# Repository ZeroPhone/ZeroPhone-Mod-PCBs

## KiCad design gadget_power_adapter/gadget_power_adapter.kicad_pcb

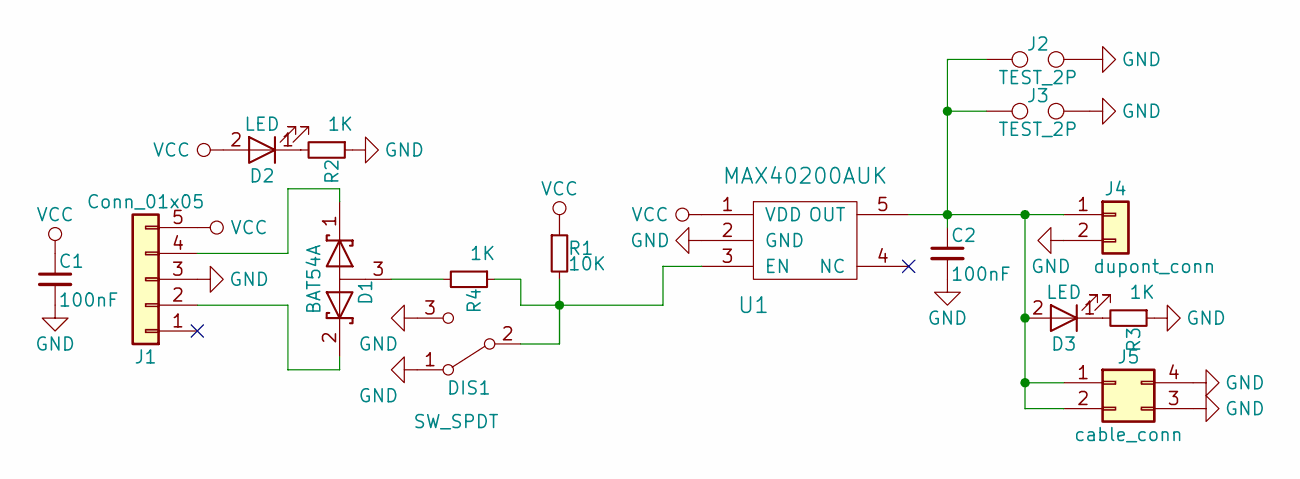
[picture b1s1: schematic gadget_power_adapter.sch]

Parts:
C1, C2: 100nF; C_0603
D1: BAT54A; SOT-23
D2, D3: LED; LED_0805
DIS1: SW_SPDT; SW_SPDT_PCM12
J1: Conn_01x05; Pin_Header_Angled_1x05_Pitch2.54mm
J2, J3: TEST_2P; Test_Point_2Pads
J4: dupont_conn; Pin_Header_Angled_1x02_Pitch2.54mm
J5: cable_conn; Pin_Header_Straight_2x02_Pitch2.54mm
R1: 10K; R_0603
R2, R3, R4: 1K; R_0603
U1: MAX40200AUK; SOT-23-5

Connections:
GND: C1.2, C2.2, DIS1.1 (A), DIS1.3 (C), J1.3, J2.2, J3.2, J4.2, J5.3, J5.4, R2.1, R3.1, U1.2 (GND)
unnamed: C2.1, D3.2 (A), J2.1, J3.1, J4.1, J5.1, J5.2, U1.5 (OUT)
unnamed: D1.1 (K), J1.4
unnamed: D1.2 (K), J1.2
unnamed: D1.3 (A), R4.2
unnamed: D2.1 (K), R2.2
unnamed: D3.1 (K), R3.2
unnamed: DIS1.2 (B), R1.2, R4.1, U1.3 (EN)
VCC: C1.1, D2.2 (A), J1.5, R1.1, U1.1 (VDD)

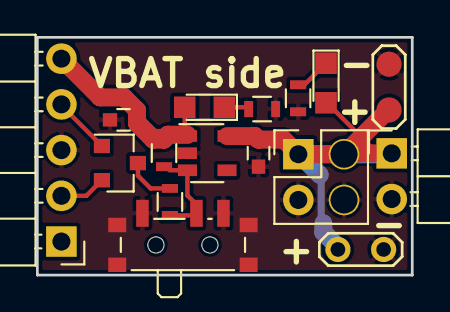
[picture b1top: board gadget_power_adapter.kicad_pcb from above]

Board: 2 copper layers, 20.8 x 13.2 mm, 16 parts (0 on the bottom side), 9 nets.

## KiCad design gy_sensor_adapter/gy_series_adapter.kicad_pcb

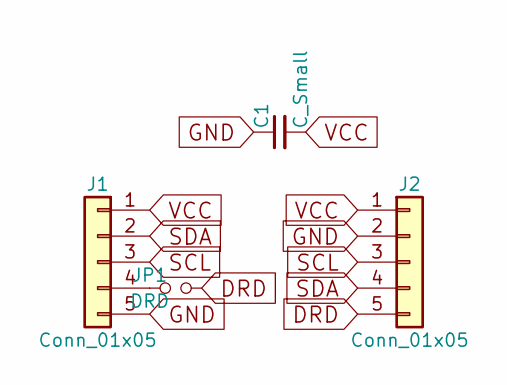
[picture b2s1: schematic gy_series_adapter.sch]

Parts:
C1: C_Small; C_0603
J1, J2: Conn_01x05; Pin_Header_Straight_1x05_Pitch2.54mm
JP1: DRD; GS2_SMALL

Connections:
DRD: J2.5, JP1.2
GND: C1.1, J1.5, J2.2
unnamed: J1.4, JP1.1
SCL: J1.3, J2.3
SDA: J1.2, J2.4
VCC: C1.2, J1.1, J2.1

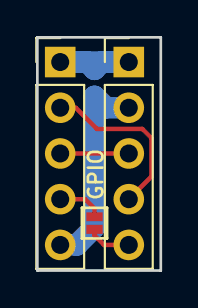
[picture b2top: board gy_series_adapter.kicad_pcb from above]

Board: 2 copper layers, 6.9 x 13.0 mm, 4 parts (1 on the bottom side), 6 nets.

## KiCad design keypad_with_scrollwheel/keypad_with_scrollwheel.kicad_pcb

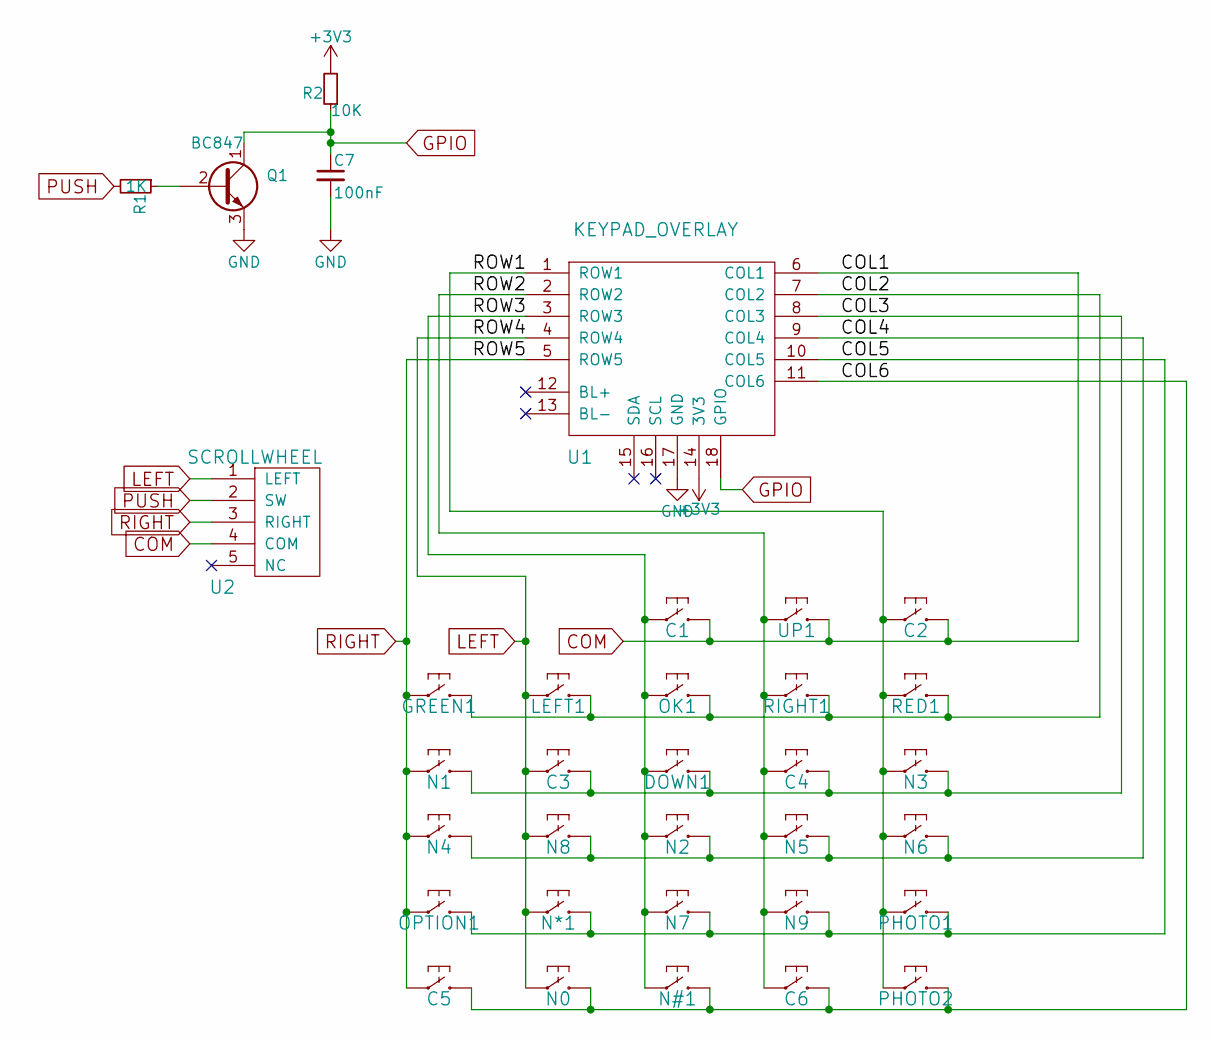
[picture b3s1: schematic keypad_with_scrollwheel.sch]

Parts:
C1, C2, C3, C4, C5, C6: AB2_SWITCH_MOMENTARY; SW_SPST_EVQPE1
C7: 100nF; C_0805
DOWN1: AB2_SWITCH_MOMENTARY; SW_SPST_SKQG
GREEN1: AB2_SWITCH_MOMENTARY; SW_SPST_EVQPE1
LEFT1: AB2_SWITCH_MOMENTARY; SW_SPST_SKQG
N0, N1, N2, N3, N4, N5, N6, N7, N8, N9: AB2_SWITCH_MOMENTARY; SW_SPST_SKQG
N#1: AB2_SWITCH_MOMENTARY; SW_SPST_SKQG
N*1: AB2_SWITCH_MOMENTARY; SW_SPST_SKQG
OK1: AB2_SWITCH_MOMENTARY; SW_SPST_SKQG
OPTION1: AB2_SWITCH_MOMENTARY; SW_SPST_EVQP7C
PHOTO1, PHOTO2: AB2_SWITCH_MOMENTARY; SW_SPST_EVQP7C
Q1: BC847; SOT-23_Handsoldering
R1: 1K; R_0805_HandSoldering
R2: 10K; R_0805_HandSoldering
RED1: AB2_SWITCH_MOMENTARY; SW_SPST_EVQPE1
RIGHT1: AB2_SWITCH_MOMENTARY; SW_SPST_SKQG
U1: KEYPAD_OVERLAY; keypad_overlay
U2: SCROLLWHEEL
UP1: AB2_SWITCH_MOMENTARY; SW_SPST_SKQG

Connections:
+3V3: R2.2, U1.14 (3V3)
/COL2: GREEN1.2, LEFT1.2, OK1.2, RED1.2, RIGHT1.2, U1.7 (COL2)
/COL3: C3.2, C4.2, DOWN1.2, N1.2, N3.2, U1.8 (COL3)
/COL4: N2.2, N4.2, N5.2, N6.2, N8.2, U1.9 (COL4)
/COL5: N7.2, N9.2, N*1.2, OPTION1.2, PHOTO1.2, U1.10 (COL5)
/COL6: C5.2, C6.2, N0.2, N#1.2, PHOTO2.2, U1.11 (COL6)
/ROW1: C2.1, N3.1, N6.1, PHOTO1.1, PHOTO2.1, RED1.1, U1.1 (ROW1)
/ROW2: C4.1, C6.1, N5.1, N9.1, RIGHT1.1, U1.2 (ROW2), UP1.1
/ROW3: C1.1, DOWN1.1, N2.1, N7.1, N#1.1, OK1.1, U1.3 (ROW3)
COM: C1.2, C2.2, U1.6 (COL1), U2.4 (COM), UP1.2
GND: C7.2, Q1.3 (E), U1.17 (GND)
GPIO: C7.1, Q1.1 (C), R2.1, U1.18 (GPIO)
LEFT: C3.1, LEFT1.1, N0.1, N8.1, N*1.1, U1.4 (ROW4), U2.1 (LEFT)
unnamed: Q1.2 (B), R1.1
PUSH: R1.2, U2.2 (SW)
RIGHT: C5.1, GREEN1.1, N1.1, N4.1, OPTION1.1, U1.5 (ROW5), U2.3 (RIGHT)

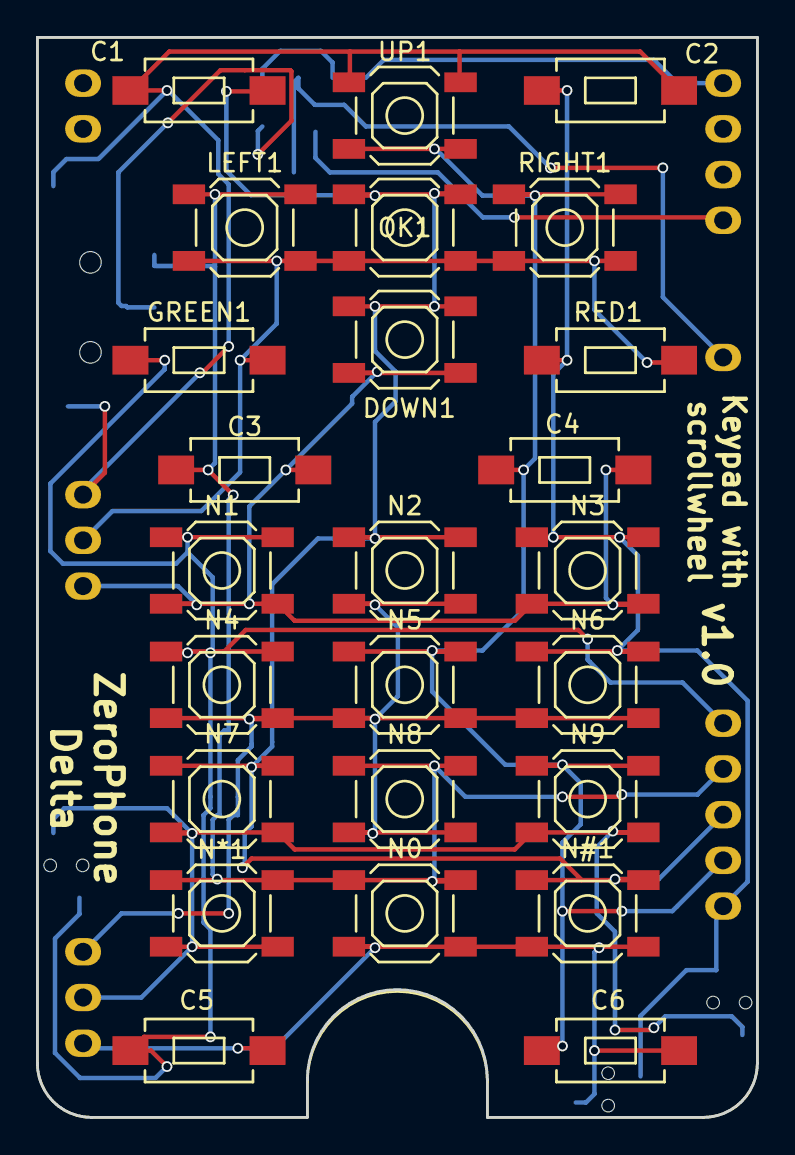
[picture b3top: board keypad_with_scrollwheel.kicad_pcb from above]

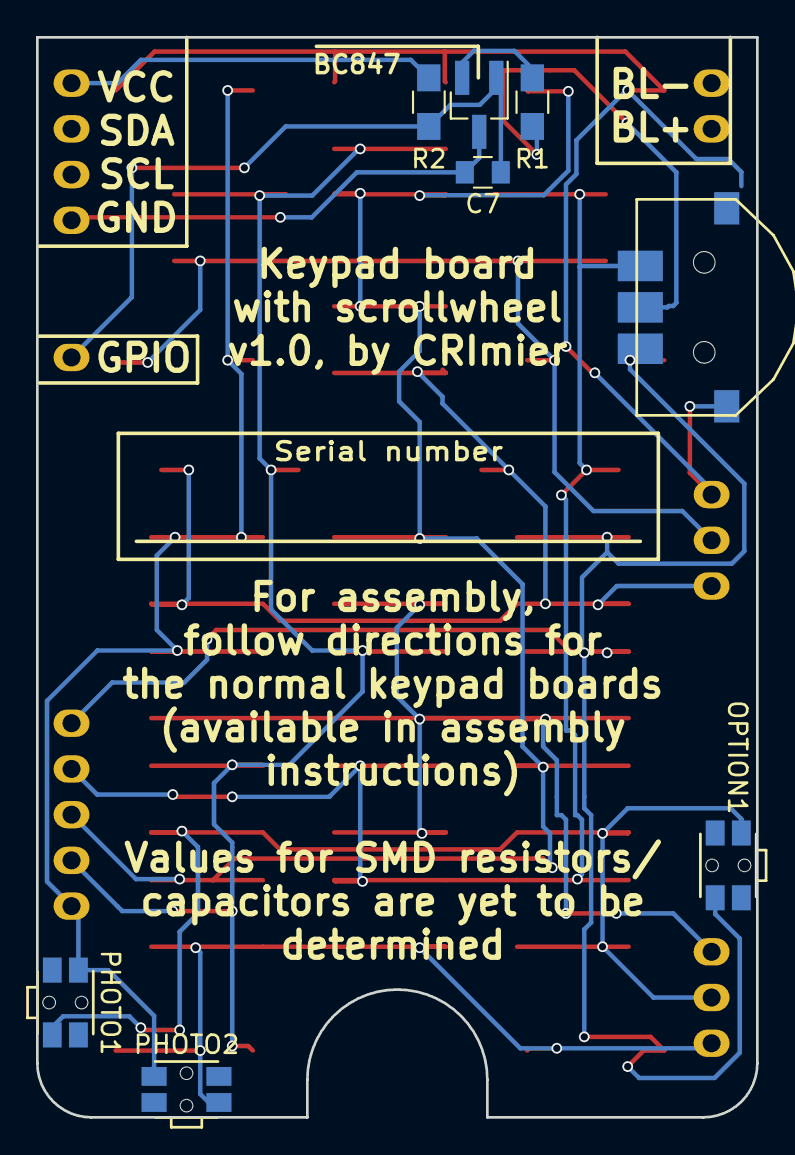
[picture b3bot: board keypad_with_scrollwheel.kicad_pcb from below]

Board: 2 copper layers, 40.0 x 60.0 mm, 34 parts (8 on the bottom side), 16 nets.

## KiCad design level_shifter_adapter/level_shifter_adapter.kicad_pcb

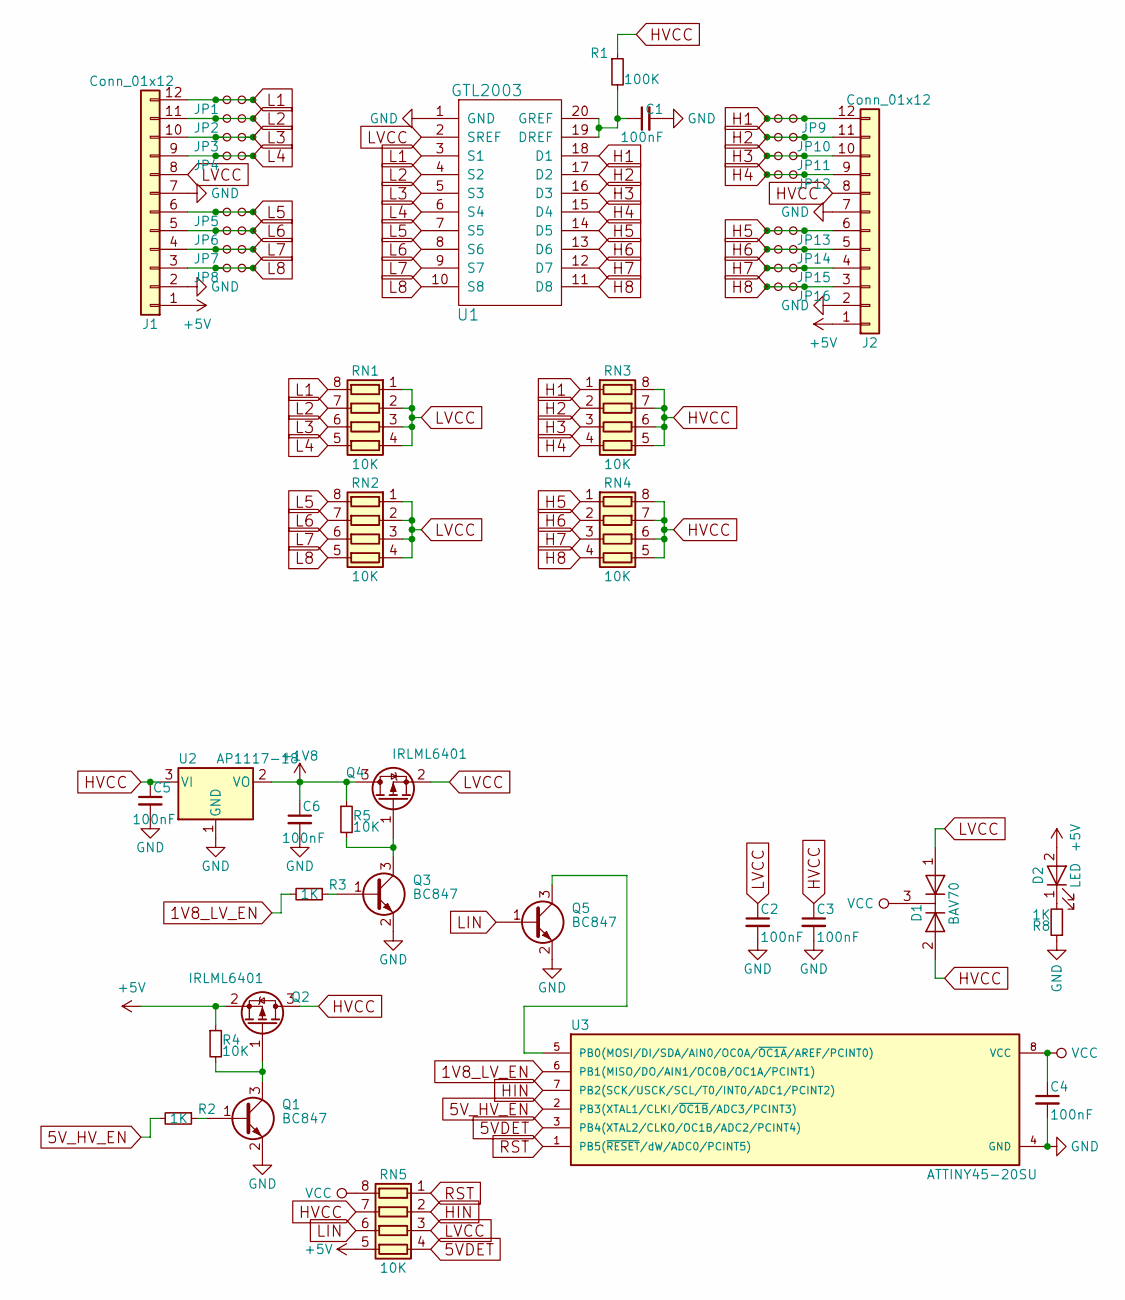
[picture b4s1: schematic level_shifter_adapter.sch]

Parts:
C1, C2, C3, C4, C5, C6: 100nF; C_0603
D1: BAV70; SOT-23
D2: LED; LED_0805
J1, J2: Conn_01x12; Pin_Header_Combined_1x12_Pitch2.54mm
JP1, JP2, JP3, JP4, JP5, JP6, JP7, JP8, JP9, JP10, JP11, JP12, JP13, JP14, JP15, JP16: J; GS2_SMALL
Q1, Q3, Q5: BC847; SOT-23
Q2, Q4: IRLML6401; SOT-23
R1: 100K; R_0603
R2, R3, R8: 1K; R_0603
R4, R5: 10K; R_0603
RN1, RN2, RN3, RN4, RN5: 10K; R_Array_Convex_4x0603
U1: GTL2003; SSOP-20_4.4x6.5mm_Pitch0.65mm
U2: AP1117-18; SOT-223-3Lead_TabPin2
U3: ATTINY45-20SU; SOIC-8_3.9x4.9mm_Pitch1.27mm

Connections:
1V8_LV_EN: R3.2, U3.6 (PB1(MISO/DO/AIN1/OC0B/OC1A/PCINT1))
5VDET: RN5.4 (R4.1), U3.3 (PB4(XTAL2/CLKO/OC1B/ADC2/PCINT4))
5V_HV_EN: R2.2, U3.2 (PB3(XTAL1/CLKI/~OC1B~/ADC3/PCINT3))
+1V8: C6.1, Q4.3 (D), R5.1, U2.2 (VO)
+5V: D2.2 (A), J1.1, J2.1, Q2.2 (S), R4.1, RN5.5 (R4.2)
GND: C1.2, C2.2, C3.2, C4.2, C5.2, C6.2, J1.2, J1.7, J2.2, J2.7, Q1.2 (E), Q3.2 (E), Q5.2 (E), R8.1, U1.1 (GND), U2.1 (GND), U3.4 (GND)
H1: J2.12, JP9.1, JP9.2, RN3.1 (R1.1), U1.18 (D1)
H2: J2.11, JP10.1, JP10.2, RN3.2 (R2.1), U1.17 (D2)
H3: J2.10, JP11.1, JP11.2, RN3.3 (R3.1), U1.16 (D3)
H4: J2.9, JP12.1, JP12.2, RN3.4 (R4.1), U1.15 (D4)
H5: J2.6, JP13.1, JP13.2, RN4.1 (R1.1), U1.14 (D5)
H6: J2.5, JP14.1, JP14.2, RN4.2 (R2.1), U1.13 (D6)
H7: J2.4, JP15.1, JP15.2, RN4.3 (R3.1), U1.12 (D7)
H8: J2.3, JP16.1, JP16.2, RN4.4 (R4.1), U1.11 (D8)
HIN: RN5.2 (R2.1), U3.7 (PB2(SCK/USCK/SCL/T0/INT0/ADC1/PCINT2))
HVCC: C3.1, C5.1, D1.2 (A), J2.8, Q2.3 (D), R1.1, RN3.5 (R4.2), RN3.6 (R3.2), RN3.7 (R2.2), RN3.8 (R1.2), RN4.5 (R4.2), RN4.6 (R3.2), RN4.7 (R2.2), RN4.8 (R1.2), RN5.7 (R2.2), U2.3 (VI)
L1: J1.12, JP1.1, JP1.2, RN1.8 (R1.2), U1.3 (S1)
L2: J1.11, JP2.1, JP2.2, RN1.7 (R2.2), U1.4 (S2)
L3: J1.10, JP3.1, JP3.2, RN1.6 (R3.2), U1.5 (S3)
L4: J1.9, JP4.1, JP4.2, RN1.5 (R4.2), U1.6 (S4)
L5: J1.6, JP5.1, JP5.2, RN2.8 (R1.2), U1.7 (S5)
L6: J1.5, JP6.1, JP6.2, RN2.7 (R2.2), U1.8 (S6)
L7: J1.4, JP7.1, JP7.2, RN2.6 (R3.2), U1.9 (S7)
L8: J1.3, JP8.1, JP8.2, RN2.5 (R4.2), U1.10 (S8)
LIN: Q5.1 (B), RN5.6 (R3.2)
LVCC: C2.1, D1.1 (A), J1.8, Q4.2 (S), RN1.1 (R1.1), RN1.2 (R2.1), RN1.3 (R3.1), RN1.4 (R4.1), RN2.1 (R1.1), RN2.2 (R2.1), RN2.3 (R3.1), RN2.4 (R4.1), RN5.3 (R3.1), U1.2 (SREF)
unnamed: C1.1, R1.2, U1.19 (DREF), U1.20 (GREF)
unnamed: D2.1 (K), R8.2
unnamed: Q1.1 (B), R2.1
unnamed: Q1.3 (C), Q2.1 (G), R4.2
unnamed: Q3.1 (B), R3.1
unnamed: Q3.3 (C), Q4.1 (G), R5.2
unnamed: Q5.3 (C), U3.5 (PB0(MOSI/DI/SDA/AIN0/OC0A/~OC1A~/AREF/P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)
RST: RN5.1 (R1.1), U3.1 (PB5(~RESET~/dW/ADC0/PCINT5))
VCC: C4.1, D1.3 (K), RN5.8 (R1.2), U3.8 (VCC)

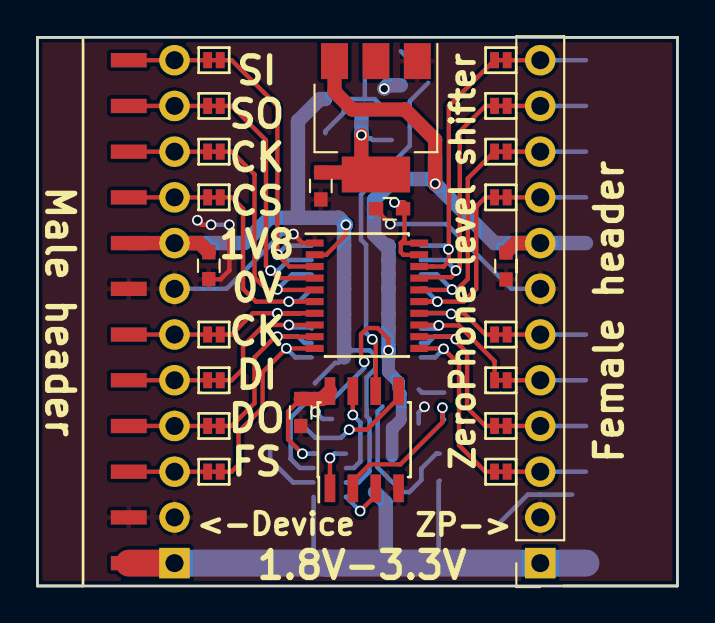
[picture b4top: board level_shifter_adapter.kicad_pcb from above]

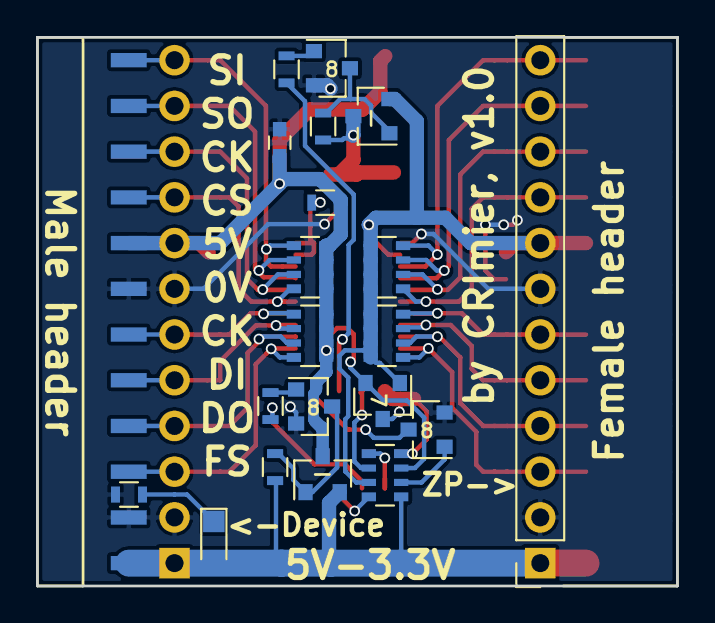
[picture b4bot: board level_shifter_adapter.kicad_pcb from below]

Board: 2 copper layers, 35.6 x 30.5 mm, 45 parts (20 on the bottom side), 35 nets.

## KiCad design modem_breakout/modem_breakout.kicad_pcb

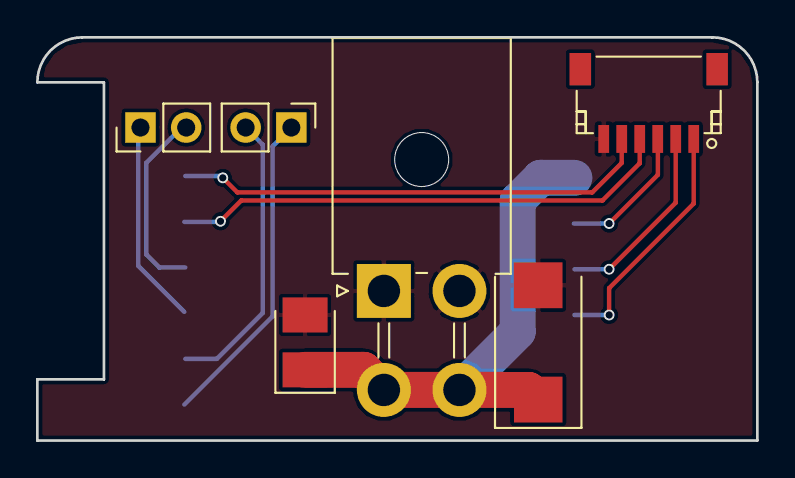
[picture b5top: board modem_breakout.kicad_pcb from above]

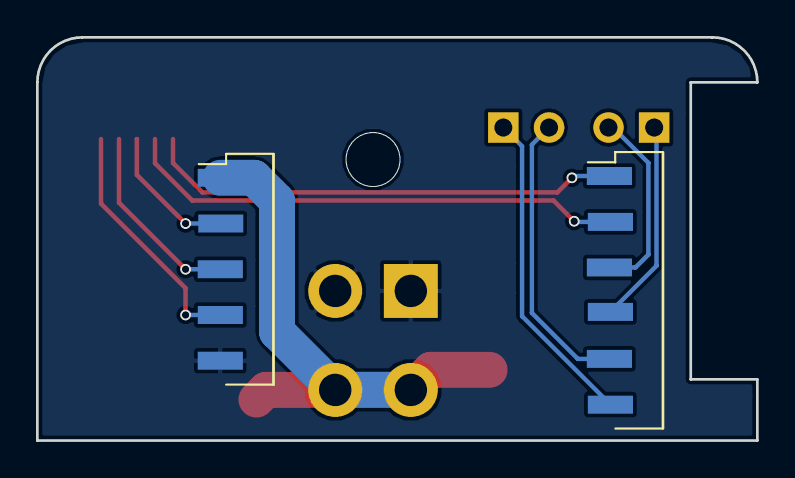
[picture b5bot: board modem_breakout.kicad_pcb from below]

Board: 2 copper layers, 40.0 x 22.4 mm, 8 parts (2 on the bottom side), 11 nets.

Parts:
C3: 100uF; CP_Tantalum_Case-D_EIA-7343-31_Reflow
C12: 10nF; CP_Tantalum_Case-B_EIA-3528-21_Reflow
J1: CONN_01X05; Pin_Header_Straight_1x05_Pitch2.54mm_SMD
J2: POWER; Molex_MiniFit-JR-5569-04A2_2x02x4.20mm_Angled
J3: Conn_02x02_Counter_Clockwise; Pin_Header_Straight_1x02_Pitch2.54mm
J4: CONN_01X06; Pin_Header_Straight_1x06_Pitch2.54mm_SMD
J5: Conn_01x02; Pin_Header_Straight_1x02_Pitch2.54mm
J6: Conn_01x06; JST_SH_SM06B-SRSS-TB_06x1.00mm_Angled

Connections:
DTR: J4.2, J6.4
GND: C3.2, C12.2, J1.5, J2.1, J2.2, J6.6
MIC+: J4.3, J5.2
MIC-: J4.4, J5.1
RESET: J1.2, J6.3
RING: J4.1, J6.5
RXD: J1.3, J6.2
SPK+: J3.2, J4.5
SPK-: J3.1, J4.6
TXD: J1.4, J6.1
VDD: C3.1, C12.1, J1.1, J2.3, J2.4

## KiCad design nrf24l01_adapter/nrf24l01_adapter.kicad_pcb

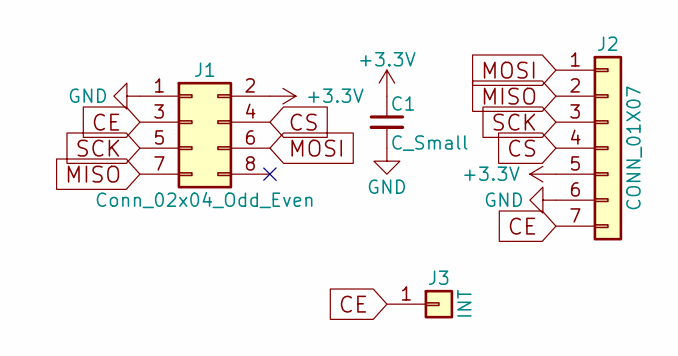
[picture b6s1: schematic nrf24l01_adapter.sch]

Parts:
C1: C_Small; C_0805_HandSoldering
J1: Conn_02x04_Odd_Even; Pin_Header_Straight_2x04_Pitch2.54mm
J2: CONN_01X07; Pin_Header_Straight_1x07_Pitch2.54mm
J3: INT; Pin_Header_Straight_1x01_Pitch2.54mm

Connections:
+3V3: C1.1, J1.2, J2.5
CE: J1.3, J2.7, J3.1
CS: J1.4, J2.4
GND: C1.2, J1.1, J2.6
MISO: J1.7, J2.2
MOSI: J1.6, J2.1
SCK: J1.5, J2.3

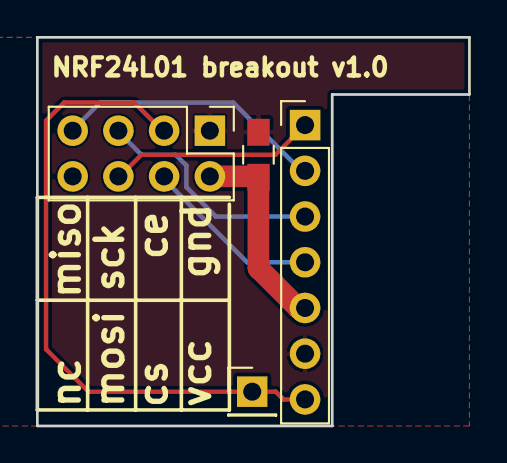
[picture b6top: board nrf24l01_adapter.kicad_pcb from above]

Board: 2 copper layers, 24.0 x 21.6 mm, 4 parts (0 on the bottom side), 7 nets.
